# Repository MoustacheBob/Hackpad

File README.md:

# Hackpad
A custom version of the Hackclubs Macropad

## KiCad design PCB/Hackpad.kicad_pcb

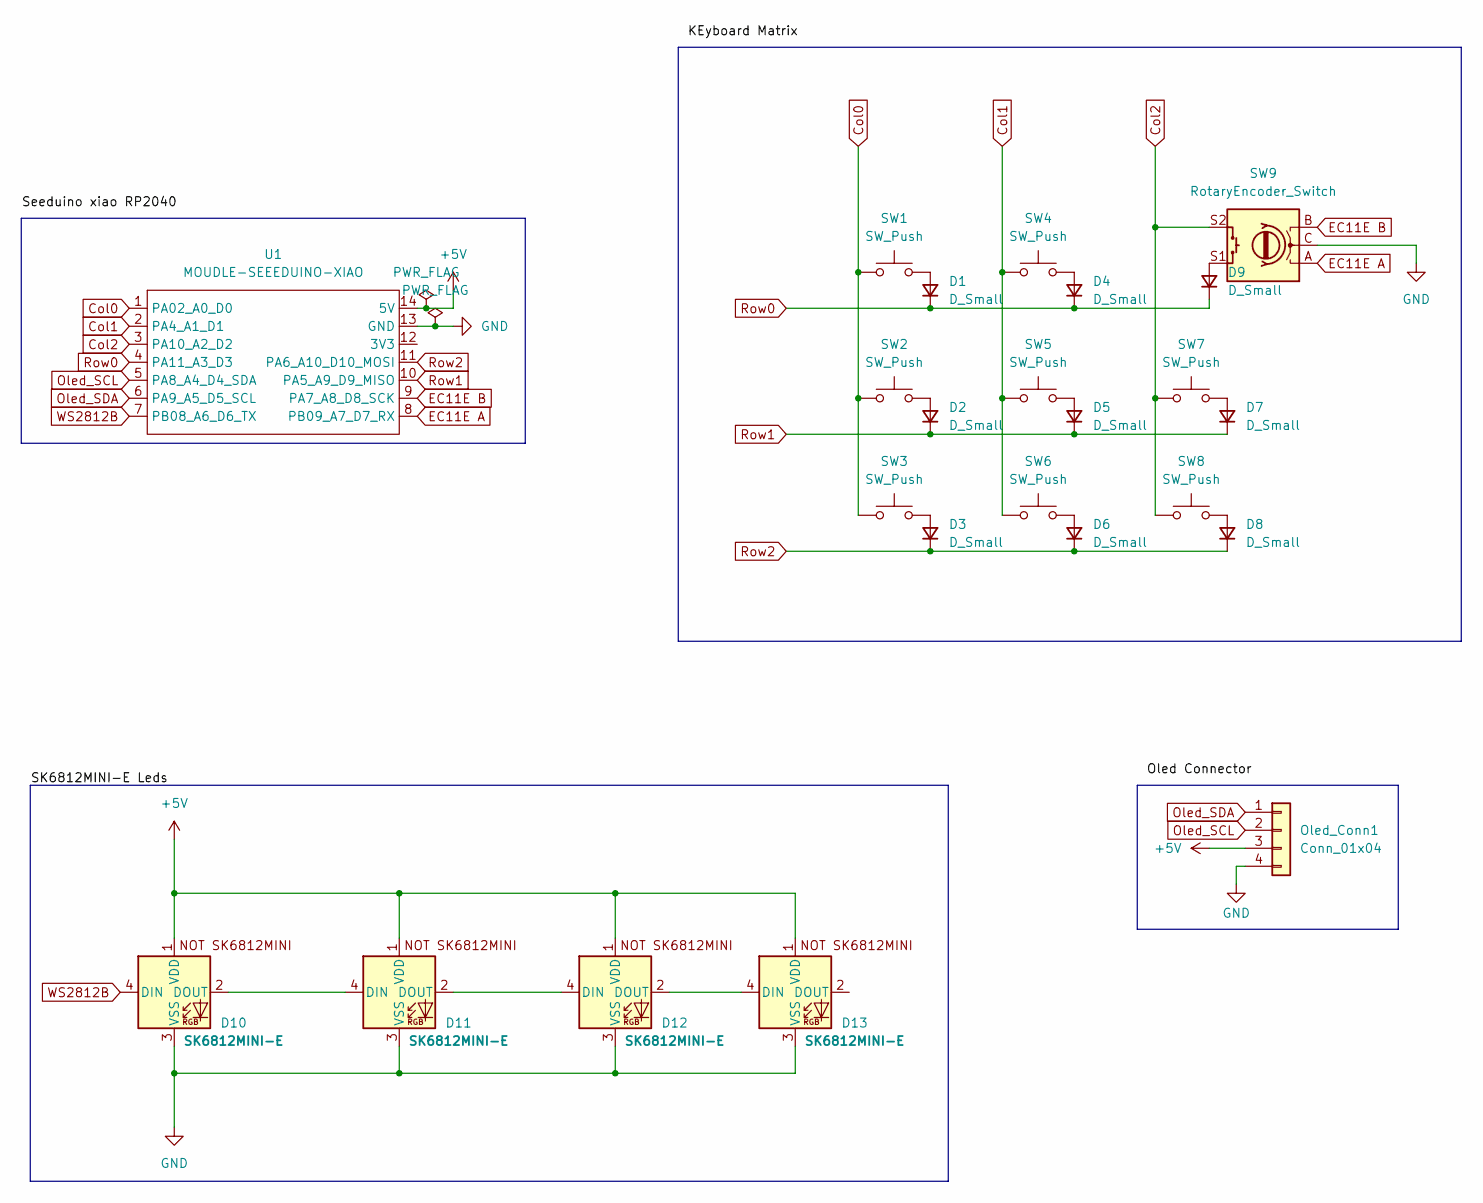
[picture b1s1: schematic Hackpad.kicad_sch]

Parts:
D1, D2, D3, D4, D5, D6, D7, D8, D9: D_Small; D_DO-41_SOD81_P10.16mm_Horizontal
D10, D11, D12, D13: SK6812MINI-E; SK6812MINI-E_fixed
Oled_Conn1: Conn_01x04; SSD1306-0.91-OLED-4pin-128x32
SW1, SW2, SW3, SW4, SW5, SW6, SW7, SW8: SW_Push; SW_MX_1u
SW9: RotaryEncoder_Switch; ROT_Alps_EC11E-Switch
U1: MOUDLE-SEEEDUINO-XIAO; XIAO-Generic-Hybrid-14P-2.54-21X17.8MM

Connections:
+5V: D10.1 (VDD), D11.1 (VDD), D12.1 (VDD), D13.1 (VDD), Oled_Conn1.3, U1.14 (5V)
Col0: SW1.1, SW2.1, SW3.1, U1.1 (PA02_A0_D0)
Col1: SW4.1, SW5.1, SW6.1, U1.2 (PA4_A1_D1)
Col2: SW7.1, SW8.1, SW9.S2, U1.3 (PA10_A2_D2)
EC11E A: SW9.A, U1.8 (PB09_A7_D7_RX)
EC11E B: SW9.B, U1.9 (PA7_A8_D8_SCK)
GND: D10.3 (VSS), D11.3 (VSS), D12.3 (VSS), D13.3 (VSS), Oled_Conn1.4, SW9.C, U1.13 (GND)
unnamed: D1.2 (A), SW1.2
unnamed: D2.2 (A), SW2.2
unnamed: D3.2 (A), SW3.2
unnamed: D4.2 (A), SW4.2
unnamed: D5.2 (A), SW5.2
unnamed: D6.2 (A), SW6.2
unnamed: D7.2 (A), SW7.2
unnamed: D8.2 (A), SW8.2
unnamed: D9.2 (A), SW9.S1
unnamed: D10.2 (DOUT), D11.4 (DIN)
unnamed: D11.2 (DOUT), D12.4 (DIN)
unnamed: D12.2 (DOUT), D13.4 (DIN)
Oled_SCL: Oled_Conn1.2, U1.5 (PA8_A4_D4_SDA)
Oled_SDA: Oled_Conn1.1, U1.6 (PA9_A5_D5_SCL)
Row0: D1.1 (K), D4.1 (K), D9.1 (K), U1.4 (PA11_A3_D3)
Row1: D2.1 (K), D5.1 (K), D7.1 (K), U1.10 (PA5_A9_D9_MISO)
Row2: D3.1 (K), D6.1 (K), D8.1 (K), U1.11 (PA6_A10_D10_MOSI)
WS2812B: D10.4 (DIN), U1.7 (PB08_A6_D6_TX)

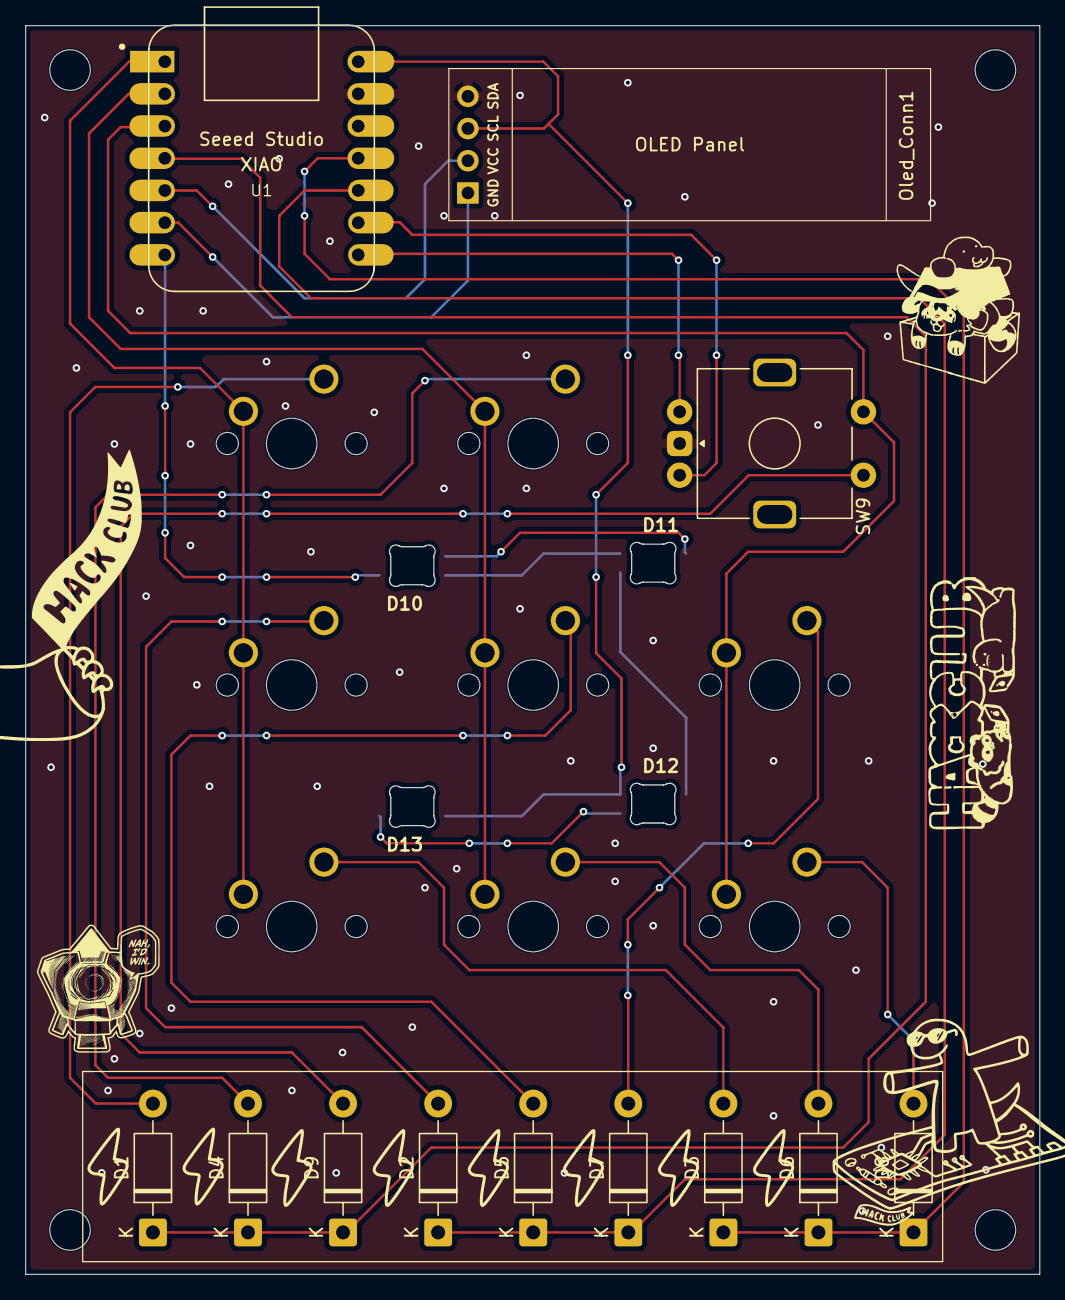
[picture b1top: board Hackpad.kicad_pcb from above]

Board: 2 copper layers, 80.0 x 98.5 mm, 24 parts (0 on the bottom side), 25 nets.
